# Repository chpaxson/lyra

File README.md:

# Lyra
## *6 axis robotic arm*
UC Berkeley MECENG 102B Project
Designed/built by Angel Garnica, David Gonzalez, Daniel Morales, Charles Paxson

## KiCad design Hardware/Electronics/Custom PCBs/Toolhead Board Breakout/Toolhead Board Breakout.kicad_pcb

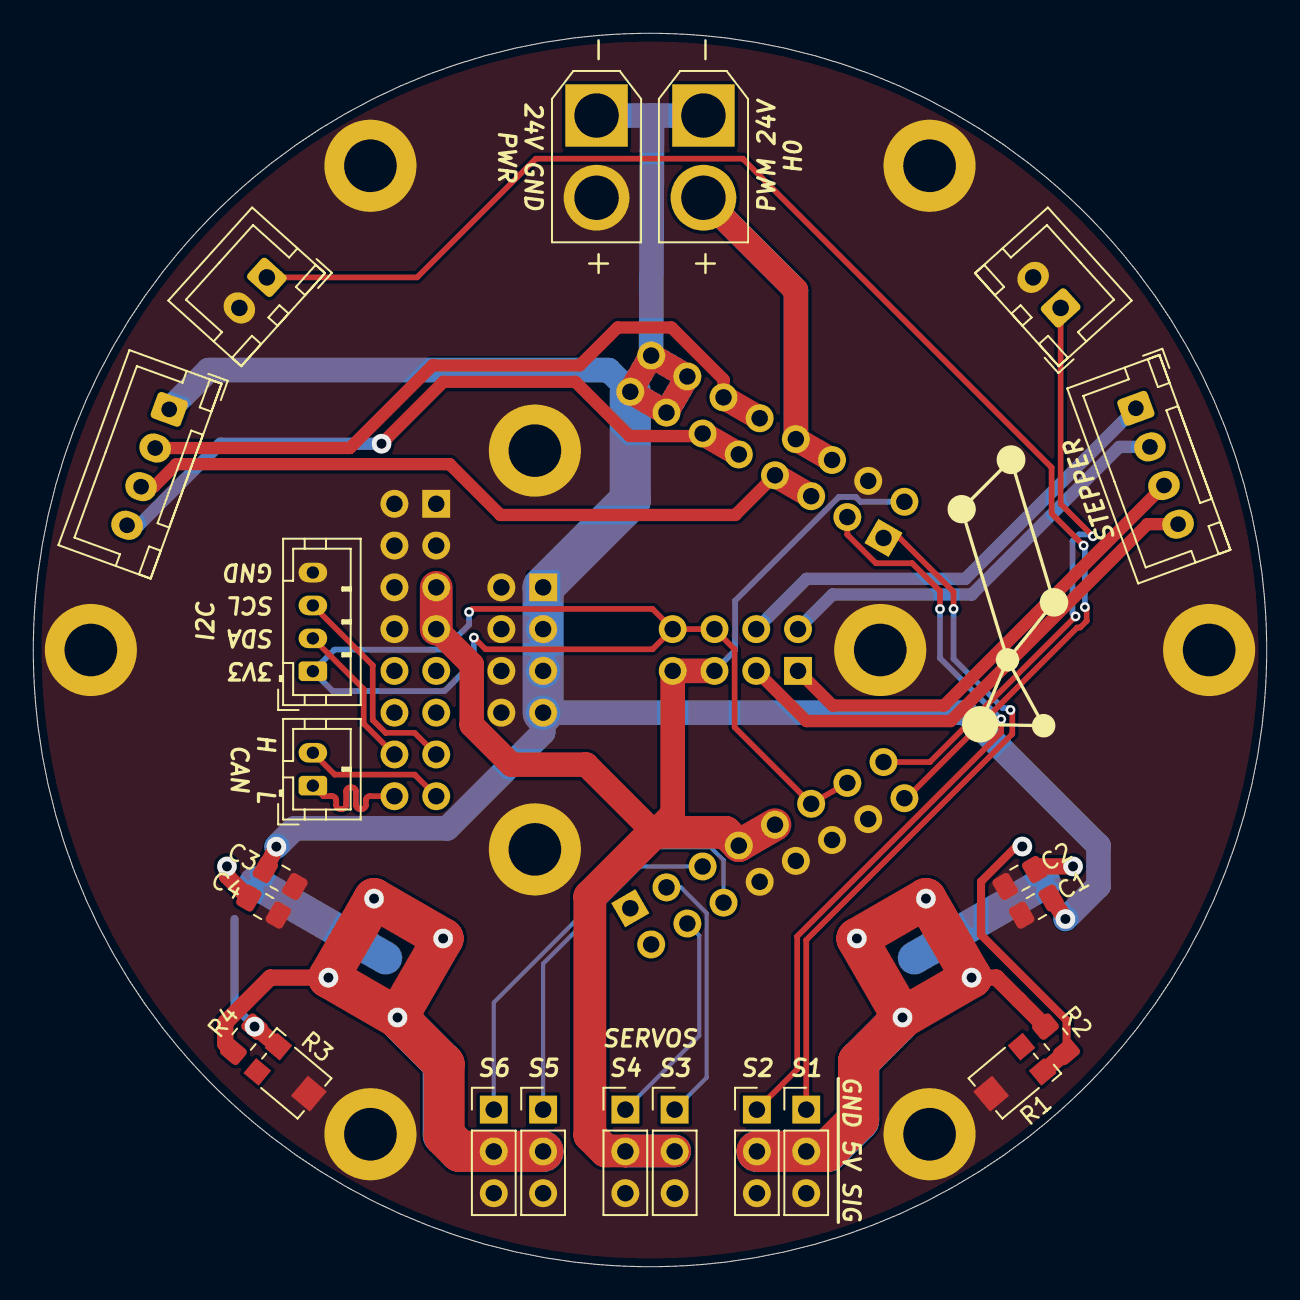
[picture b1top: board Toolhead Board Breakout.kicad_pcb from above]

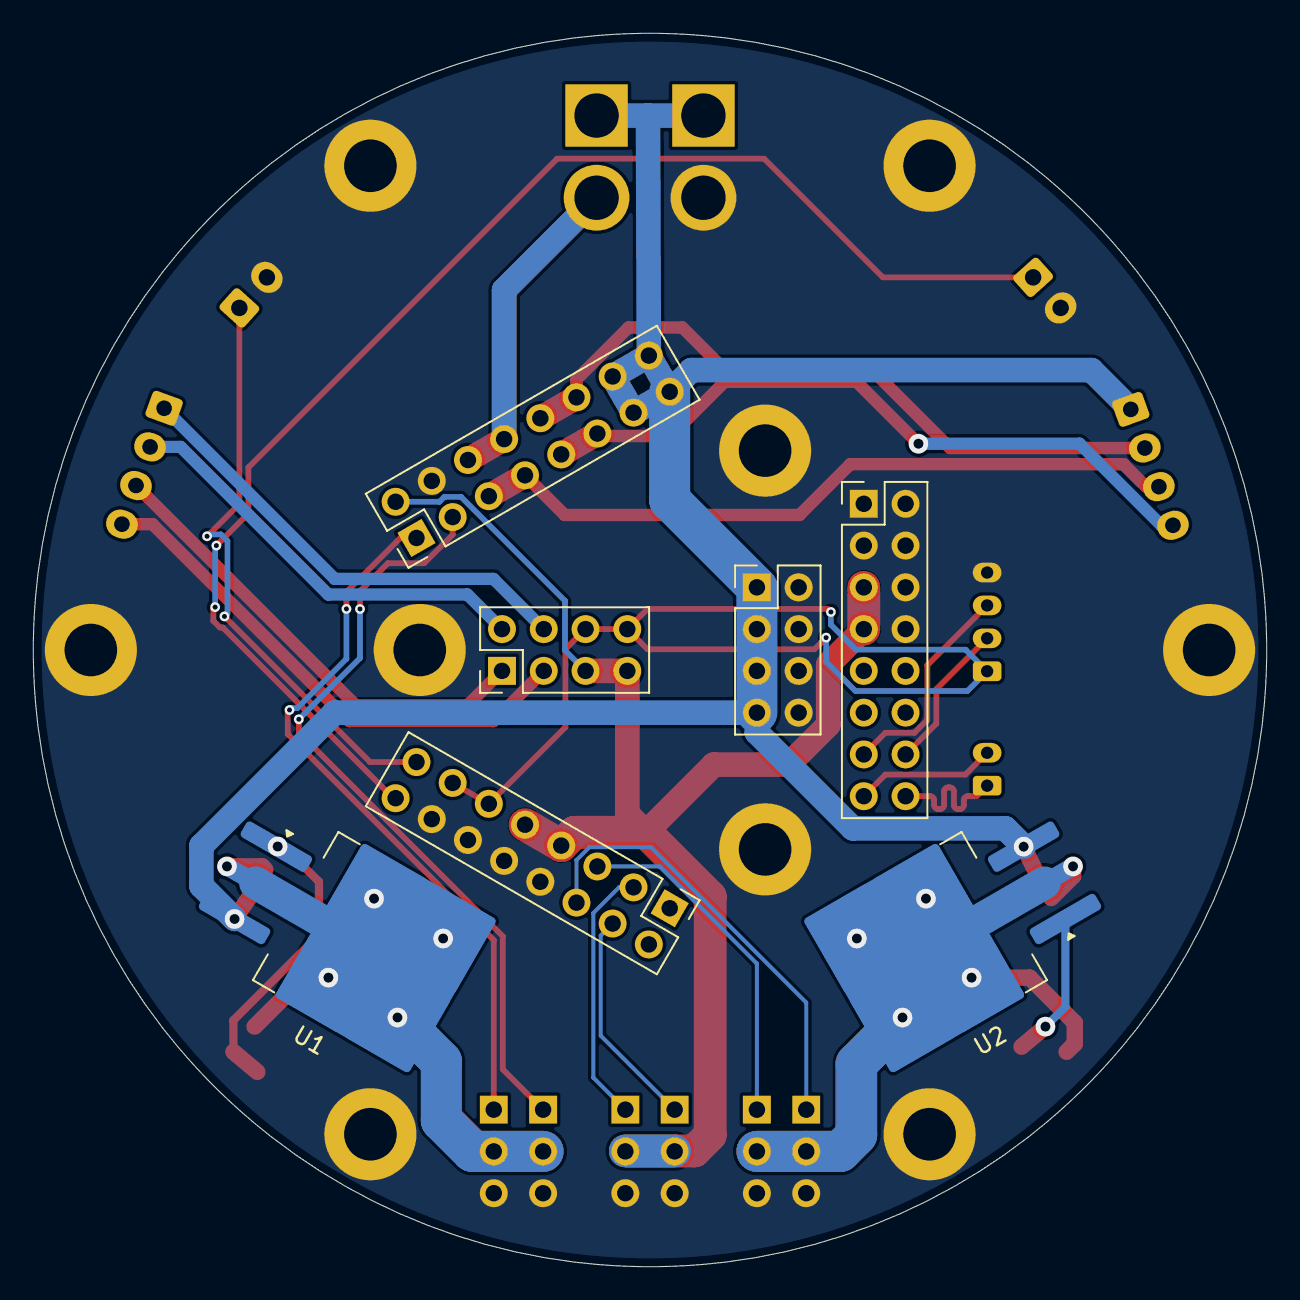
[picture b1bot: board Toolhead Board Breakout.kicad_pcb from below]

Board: 2 copper layers, 75.0 x 75.0 mm, 38 parts (7 on the bottom side), 28 nets.

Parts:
C1, C2, C3, C4: 10uF; C_0805_2012Metric_Pad1.18x1.45mm_HandSolder
H1, H1#2, H1#3, H2, H2#2, H2#3, H2#4, H2#5, H2#6: MountingHole; MountingHole_3.2mm_M3_DIN965_Pad
J1, J2, J3: Conn_02x08_Odd_Even; PinHeader_2x08_P2.54mm_Vertical
J4, J5: Conn_02x04_Odd_Even; PinHeader_2x04_P2.54mm_Vertical
J6, J22: Conn_01x04; JST_XH_B4B-XH-A_1x04_P2.50mm_Vertical
J7, J8, J9, J10, J11, J12: Conn_01x03; PinHeader_1x03_P2.54mm_Vertical
J13: Conn_01x02; JST_PH_B2B-PH-K_1x02_P2.00mm_Vertical
J14: Conn_01x04; JST_PH_B4B-PH-K_1x04_P2.00mm_Vertical
J15, J21: Conn_01x02; AMASS_XT30U-F_1x02_P5.0mm_Vertical
J17, J18: Conn_01x02; JST_XH_B2B-XH-A_1x02_P2.50mm_Vertical
R1, R3: 5k; Potentiometer_Bourns_TC33X_Vertical
R2, R4: 121; R_0805_2012Metric_Pad1.20x1.40mm_HandSolder
U1, U2: LM1084-5.0; TO-263-3_TabPin2

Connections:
5VA: C2.1, J7.2, J8.2, R2.1, U1.2 (VO)
5VB: C4.1, J11.2, J12.2, R4.1, U2.2 (VO)
24V_PWM0: J2.6, J2.8, J21.2
24V_PWM1: J2.10, J2.12, J22.2
24V_PWM2: J2.5, J2.7, J22.3
24V_PWM3: J2.9, J2.11, J22.4
+3.3V: J3.11, J3.13, J5.6, J5.8, J14.1
+5V: J1.5, J1.7, J2.2, J3.7, J3.9, J5.5, J5.7, J9.2, J10.2
+24V: C1.1, C3.1, J2.13, J2.14, J2.15, J2.16, J4.1, J4.3, J4.5, J4.7, J15.1, J21.1, J22.1, U1.3 (VI), U2.3 (VI)
CAN_H: J1.16, J13.1
CAN_L: J1.15, J13.2
GND: C1.2, C2.2, C3.2, C4.2, H1.1, H1#2.1, H1#3.1, H2.1, H2#2.1, H2#3.1, H2#4.1, H2#5.1, H2#6.1, J1.1, J1.2, J1.3, J1.4, J1.6, J1.8, J2.4, J3.8, J3.10, J3.12, J3.14, J4.2, J4.4, J4.6, J4.8, J7.3, J8.3, J9.3, J10.3, J11.3, J12.3, J14.4, J15.2, J17.2, J18.2, R1.2, R3.2
unnamed: R1.1, R2.2, U1.1 (GND)
unnamed: R3.1, R4.2, U2.1 (GND)
OA1: J5.4, J6.1
OA2: J5.2, J6.2
OB1: J5.1, J6.3
OB2: J5.3, J6.4
SCL: J1.13, J14.3
SDA: J1.14, J14.2
SERVO1: J2.1, J7.1
SERVO2: J2.3, J8.1
SERVO3: J3.3, J9.1
SERVO4: J3.4, J10.1
SERVO5: J3.5, J11.1
SERVO6: J3.6, J12.1
THERM0: J3.15, J17.1
THERM1: J3.16, J18.1

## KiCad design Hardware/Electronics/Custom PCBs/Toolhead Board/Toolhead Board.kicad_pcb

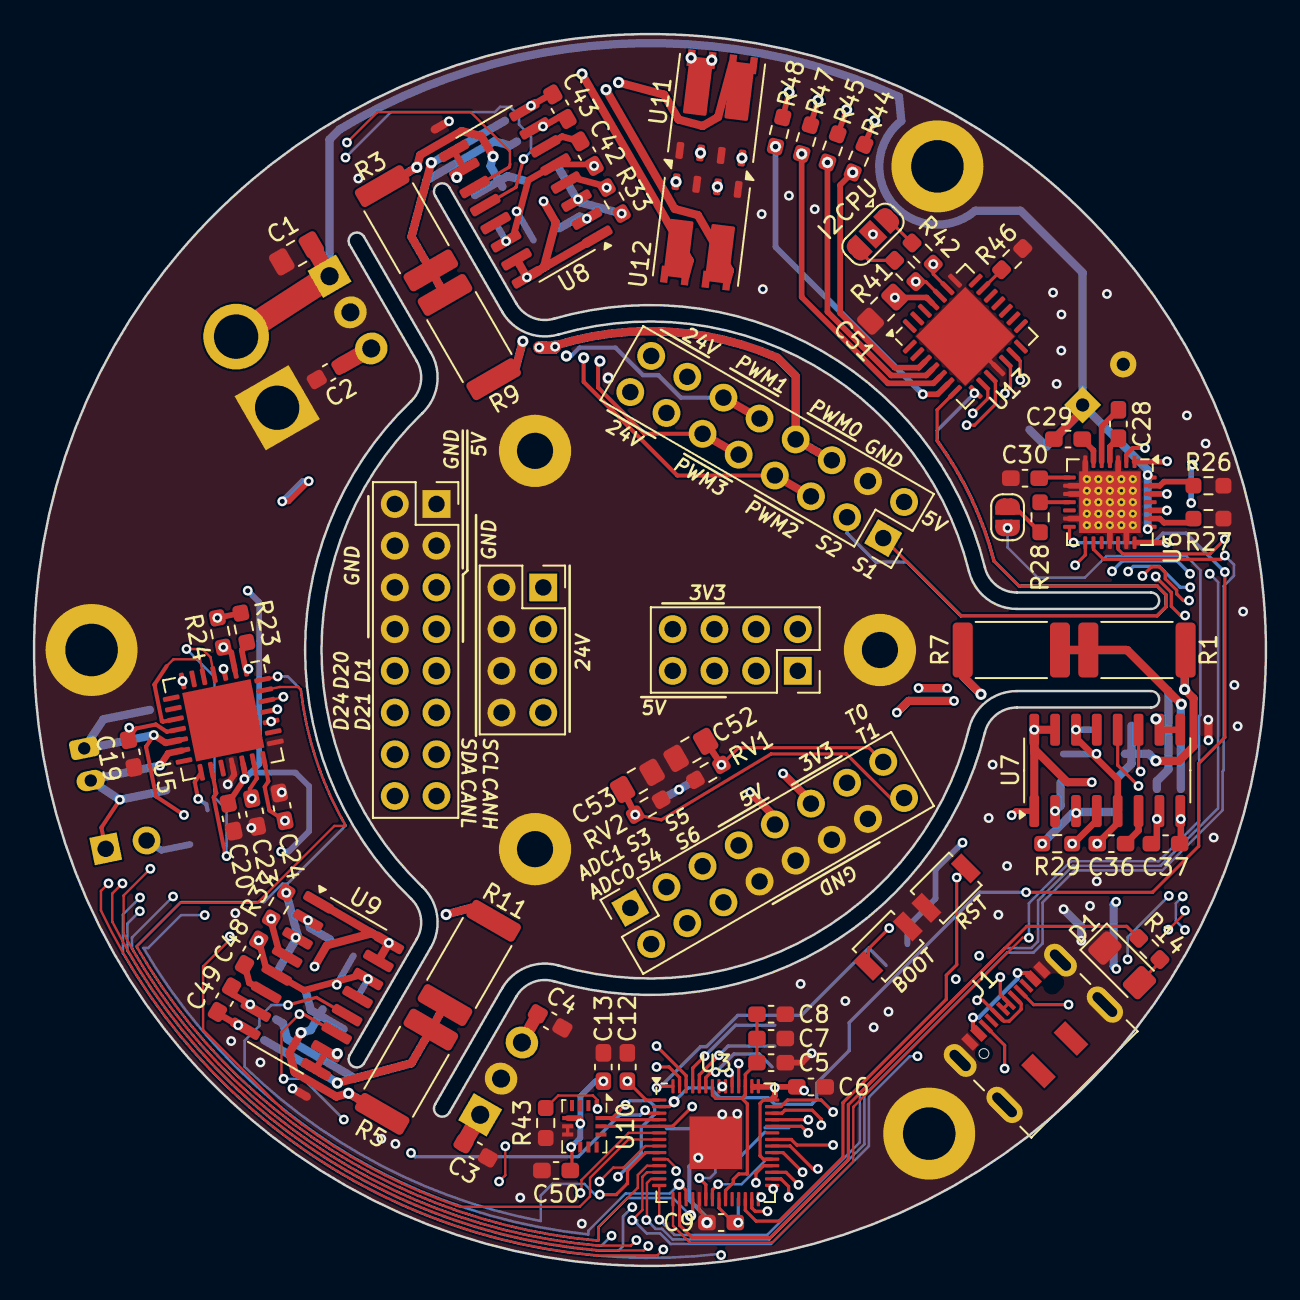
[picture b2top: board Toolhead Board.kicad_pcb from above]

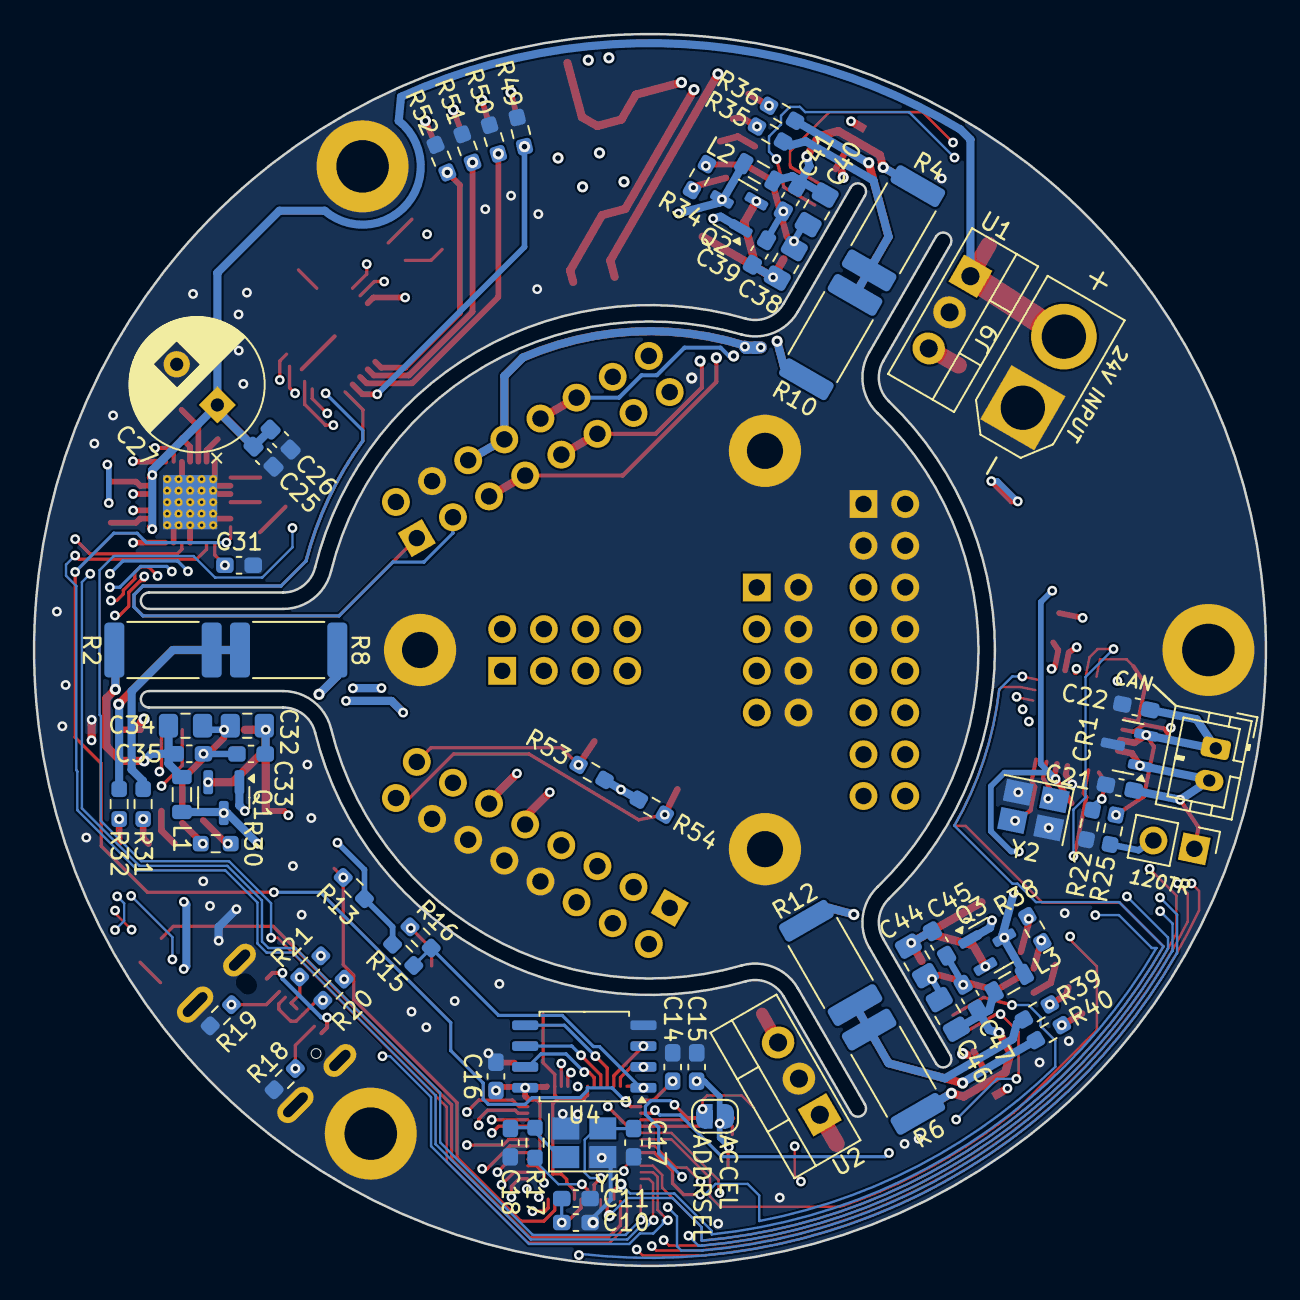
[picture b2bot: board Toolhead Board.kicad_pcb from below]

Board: 4 copper layers, 75.0 x 75.0 mm, 155 parts (72 on the bottom side), 124 nets.

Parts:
C1: 1u/100V; C_0805_2012Metric_Pad1.18x1.45mm_HandSolder
C2, C3, C4, C5, C6: 1u; C_0603_1608Metric_Pad1.08x0.95mm_HandSolder
C7, C8, C9, C10, C11, C12, C13, C14, C15, C16, C19, C20, C25, C26, C29, C31, C50: 100n; C_0603_1608Metric_Pad1.08x0.95mm_HandSolder
C17, C18, C23, C24: 22p; C_0603_1608Metric_Pad1.08x0.95mm_HandSolder
C21, C22: 47p; C_0603_1608Metric_Pad1.08x0.95mm_HandSolder
C27: 100u; CP_Radial_D8.0mm_P3.50mm
C28: 22n; C_0603_1608Metric_Pad1.08x0.95mm_HandSolder
C30: 4.7u; C_0603_1608Metric_Pad1.08x0.95mm_HandSolder
C32, C34, C38, C40, C44, C46: 10uF; C_0805_2012Metric_Pad1.18x1.45mm_HandSolder
C33, C35, C36, C37, C39, C41, C42, C43, C45, C47, C48, C49: 0.1uF; C_0603_1608Metric_Pad1.08x0.95mm_HandSolder
C51, C52, C53: 10u; C_0805_2012Metric_Pad1.18x1.45mm_HandSolder
CR1: PESD1CAN_215; SOT-23
D1: LED; LED_1206_3216Metric_Pad1.42x1.75mm_HandSolder
H1, H1#2, H1#3: MountingHole; MountingHole_3.2mm_M3_DIN965_Pad
H2, H2#2, H2#3: MountingHole; MountingHole_2.2mm_M2_Pad
J1: USB C Receptacle; USB_C_Receptacle_JAE_DX07S016JA1R1500
J2, J6: Conn_02x04_Odd_Even; PinSocket_2x04_P2.54mm_Vertical
J3, J4, J5: Conn_02x08_Odd_Even; PinSocket_2x08_P2.54mm_Vertical
J7: Conn_01x02; JST_PH_B2B-PH-K_1x02_P2.00mm_Vertical
J8: Conn_01x02; PinHeader_1x02_P2.54mm_Vertical
J9: Conn_01x02; AMASS_XT30U-F_1x02_P5.0mm_Vertical
JP1, JP3: SolderJumper_2_Open; SolderJumper-2_P1.3mm_Open_RoundedPad1.0x1.5mm
JP2: SolderJumper_3_Bridged123; SolderJumper-3_P1.3mm_Open_RoundedPad1.0x1.5mm
L1, L2, L3: 3.3uH; L_0805_2012Metric
NT1, NT2, NT3: NetTie_2; NetTie-2_SMD_Pad0.5mm
Q1, Q2, Q3: MMBT4403; SOT-23
R1, R2, R3, R4, R5, R6, R7, R8, R9, R10, R11, R12: 330; R_2512_6332Metric
R13, R14, R15, R22, R23, R24, R29, R33, R37, R43, R46, R49, R50, R51, R52: 10k; R_0603_1608Metric_Pad0.98x0.95mm_HandSolder
R16, R17: 1k; R_0603_1608Metric_Pad0.98x0.95mm_HandSolder
R18, R19: 5.1k; R_0603_1608Metric_Pad0.98x0.95mm_HandSolder
R20, R21: 27.4; R_0603_1608Metric_Pad0.98x0.95mm_HandSolder
R25: 120; R_0603_1608Metric_Pad0.98x0.95mm_HandSolder
R26, R27: 0R11; R_0603_1608Metric_Pad0.98x0.95mm_HandSolder
R28, R31, R32, R35, R36, R39, R40, R44, R45, R47, R48: 100; R_0603_1608Metric_Pad0.98x0.95mm_HandSolder
R30, R34, R38: 8.2k; R_0603_1608Metric_Pad0.98x0.95mm_HandSolder
R41, R42, R53, R54: 2.2k; R_0603_1608Metric_Pad0.98x0.95mm_HandSolder
RV1, RV2: CG0603MLC-3.3LE; R_0603_1608Metric_Pad0.98x0.95mm_HandSolder
SW1: BOOT; SW_SPST_B3U-1000P
SW2: RESET; SW_SPST_B3U-1000P
U1, U2: LF15_TO220; TO-220-3_Vertical
U3: RP2040; QFN-56-1EP_7x7mm_P0.4mm_EP3.2x3.2mm
U4: W25Q128JVS; SOIC-8_5.23x5.23mm_P1.27mm
U5: MCP25625-x-SS; QFN-28-1EP_6x6mm_P0.65mm_EP4.25x4.25mm
U6: TMC2209-LA; QFN-28-1EP_5x5mm_P0.5mm_EP3.75x3.75mm_ThermalVias
U7, U8, U9: HX711; SOIC-16_3.9x9.9mm_P1.27mm
U10: BMI270; Bosch_LGA-14_3x2.5mm_P0.5mm
U11, U12: G20N06D52; WDFN-8-1EP_6x5mm_P1.27mm_EP3.4x4mm_No_Center_Pad
U13: PCA9685BS; QFN-28-1EP_6x6mm_P0.65mm_EP4.25x4.25mm
Y1: 12MHz/12pF/50Ω/20ppm; Oscillator_SMD_SeikoEpson_SG210-4Pin_2.5x2.0mm_HandSoldering
Y2: 16MHz/12pF; Oscillator_SMD_SeikoEpson_SG210-4Pin_2.5x2.0mm_HandSoldering

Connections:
24V_PWM0: J4.6, J4.8, U11.7 (D1)
24V_PWM1: J4.10, J4.12, U11.5 (D2)
24V_PWM2: J4.5, J4.7, U12.7 (D1)
24V_PWM3: J4.9, J4.11, U12.5 (D2)
+1V1: C5.2, C7.2, C8.2, U3.23 (DVDD), U3.45 (VREG_VOUT), U3.50 (DVDD)
+3.3V: C4.1, C6.1, C9.2, C10.2, C11.2, C12.2, C13.2, C14.2, C15.2, C16.1, C19.2, C31.1, C32.1, C33.1, C38.1, C39.1, C44.1, C45.1, C50.1, J5.11, J5.13, J6.6, J6.8, JP2.2 (C), JP3.1 (A), Q1.2 (E), Q2.2 (E), Q3.2 (E), R13.1, R15.2, R23.1, R24.2, R53.1, R54.1, U2.3 (VO), U3.1 (IOVDD), U3.10 (IOVDD), U3.22 (IOVDD), U3.33 (IOVDD), U3.42 (IOVDD), U3.43 (ADC_AVDD), U3.44 (VREG_IN), U3.48 (USB_VDD), U3.49 (IOVDD), U4.8 (VCC), U5.3 (VDD), U5.11 (VIO), U6.15 (VCC_IO), U7.1 (VSUP), U7.15 (RATE), U7.16 (DVDD), U8.1 (VSUP), U8.15 (RATE), U8.16 (DVDD), U9.1 (VSUP), U9.15 (RATE), U9.16 (DVDD), U10.5 (VDDIO), U10.8 (VDD)
+5V: C2.1, C3.1, C20.1, C51.2, J3.5, J3.7, J4.2, J5.7, J5.9, J6.5, J6.7, U1.3 (VO), U2.1 (VI), U5.19 (VDDA), U13.25 (VDD)
/Accelerometer/Address Selection: JP3.2 (B), R43.1, U10.1 (SDO)
/Microcontroller/LED: R14.2, U3.16 (GPIO13)
/Microcontroller/QSPI_SCK: U3.52 (QSPI_SCLK), U4.6 (CLK)
/Microcontroller/QSPI_SD0: U3.53 (QSPI_SD0), U4.5 (DI(IO0))
/Microcontroller/QSPI_SD1: U3.55 (QSPI_SD1), U4.2 (DO(IO1))
/Microcontroller/QSPI_SD2: U3.54 (QSPI_SD2), U4.3 (IO2)
/Microcontroller/QSPI_SD3: U3.51 (QSPI_SD3), U4.7 (IO3)
/Microcontroller/QSPI_SS: R15.1, R16.2, U3.56 (QSPI_SS), U4.1 (~CS)
/Microcontroller/RUN: R13.2, SW2.2, U3.26 (RUN)
/Microcontroller/USB+: R20.2, U3.47 (USB_DP)
/Microcontroller/USB-: R21.1, U3.46 (USB_DM)
/Microcontroller/~USB_BOOT: R16.1, SW1.2
ADC0: J5.2, U3.38 (GPIO26_ADC0)
ADC1: J5.1, U3.39 (GPIO27_ADC1)
CAN_CS: R23.2, U3.30 (GPIO19), U5.1 (~CS)
CAN_H: C21.1, CR1.1, J3.16, J7.2, J8.1, U5.13 (CANH)
CAN_INT: U3.34 (GPIO22), U5.25 (~INT)
CAN_L: C22.1, CR1.2, J3.15, J7.1, R25.2, U5.12 (CANL)
CAN_RST: R24.1, U3.29 (GPIO18), U5.2 (~RESET)
CAN_STBY: R22.2, U3.27 (GPIO16), U5.15 (STBY)
D1: J3.9, U3.3 (GPIO1)
D20: J3.10, U3.31 (GPIO20)
D21: J3.11, U3.32 (GPIO21)
D24: J3.12, U3.36 (GPIO24)
GND: C1.1, C2.2, C3.2, C4.2, C5.1, C6.2, C7.1, C8.1, C9.1, C10.1, C11.1, C12.1, C13.1, C14.1, C15.1, C16.2, C17.1, C18.1, C19.1, C20.2, C21.2, C22.2, C23.1, C24.2, C25.2, C26.2, C27.2, C30.1, C31.2, C50.2, C51.1, C52.2, C53.2, CR1.3, D1.1 (K), H1.1, H1#2.1, H1#3.1, H2.1, H2#2.1, H2#3.1, J1.A1 (GND), J1.A12 (GND), J1.B1 (GND), J1.B12 (GND), J1.S1 (SHIELD), J2.2, J2.4, J2.6, J2.8, J3.1, J3.2, J3.3, J3.4, J3.6, J3.8, J4.4, J5.8, J5.10, J5.12, J5.14, J9.1, NT1.2, NT2.2, NT3.2, R18.2, R19.2, R22.1, R26.2, R27.1, R43.2, R46.1, R49.1, R50.1, R51.1, R52.1, RV1.2, RV2.2, SW1.1, SW2.1, U1.2 (GND), U2.2 (GND), U3.19 (TESTEN), U3.57 (GND), U4.4 (GND), U5.18 (VSS), U5.22 (GND), U6.3 (GND), U6.7 (SPREAD), U6.9 (MS1_AD0), U6.10 (MS2_AD1), U6.13 (CLK), U6.18 (GND), U6.20 (STDBY), U6.29 (GND), U10.6 (GNDIO), U10.7 (GND), U11.1 (S1), U11.3 (S2), U12.1 (S1), U12.3 (S2), U13.11 (VSS), U13.22 (EXTCLK), U13.29 (VSS), Y1.2, Y1.4, Y2.2, Y2.4
MISO: U3.11 (GPIO8), U5.27 (SI)
MOSI: U3.18 (GPIO15), U5.28 (SO)
MOT_DIAG: JP1.1 (A), U3.15 (GPIO12)
MOT_DIR: U3.14 (GPIO11), U6.19 (DIR)
MOT_EN: U3.12 (GPIO9), U6.2 (ENN)
MOT_STP: U3.13 (GPIO10), U6.16 (STEP)
MOT_UART: U3.2 (GPIO0), U6.14 (PDN_UART)
unnamed: C18.2, R17.1, Y1.1
unnamed: D1.2 (A), R14.1
unnamed: J1.A5 (CC1), R18.1
unnamed: J1.B5 (CC2), R19.1
unnamed: J1.A6 (D+), J1.B6 (D+), R21.2
unnamed: J1.A7 (D-), J1.B7 (D-), R20.1
unnamed: J8.2, R25.1
unnamed: JP1.2 (B), R28.1
unnamed: JP2.1 (A), R42.1
unnamed: JP2.3 (B), R41.1
unnamed: Q1.1 (B), U7.2 (BASE)
unnamed: L1.1, Q1.3 (C), R29.1, U7.3 (AVDD)
unnamed: Q2.1 (B), U8.2 (BASE)
unnamed: L2.1, Q2.3 (C), R33.1, U8.3 (AVDD)
unnamed: Q3.1 (B), U9.2 (BASE)
unnamed: L3.1, Q3.3 (C), R37.1, U9.3 (AVDD)
unnamed: C17.2, U3.20 (XIN), Y1.3
unnamed: R17.2, U3.21 (XOUT)
unnamed: C24.1, U5.21 (OSC1), Y2.3
unnamed: C23.2, U5.20 (OSC2), Y2.1
unnamed: U5.5 (RxCAN), U5.10 (RXD)
unnamed: U5.4 (TxCAN), U5.16 (TXD)
unnamed: C30.2, U6.8 (5VOUT)
unnamed: R27.2, U6.23 (BRA)
unnamed: R26.1, U6.27 (BRB)
unnamed: C28.1, U6.5 (CPI)
unnamed: C28.2, U6.4 (CPO)
unnamed: R28.2, U6.11 (DIAG)
unnamed: C29.2, U6.6 (VCP)
unnamed: C37.1, R32.2, U7.8 (INA+)
unnamed: C37.2, R31.1, U7.7 (INA-)
unnamed: C36.2, U7.6 (VBG)
unnamed: R29.2, R30.1, U7.4 (VFB)
unnamed: C43.1, R36.2, U8.8 (INA+)
unnamed: C43.2, R35.1, U8.7 (INA-)
unnamed: C42.2, U8.6 (VBG)
unnamed: R33.2, R34.1, U8.4 (VFB)
unnamed: C49.1, R40.2, U9.8 (INA+)
unnamed: C49.2, R39.1, U9.7 (INA-)
unnamed: C48.2, U9.6 (VBG)
unnamed: R37.2, R38.1, U9.4 (VFB)
unnamed: R44.2, U11.2 (G1)
unnamed: R45.2, U11.4 (G2)
unnamed: R47.2, U12.2 (G1)
unnamed: R48.2, U12.4 (G2)
unnamed: R44.1, R52.2, U13.3 (LED0)
unnamed: R45.1, R51.2, U13.4 (LED1)
unnamed: R47.1, R50.2, U13.5 (LED2)
unnamed: R48.1, R49.2, U13.6 (LED3)
unnamed: R46.2, U13.20 (~OE)
OA1: J6.4, U6.24 (OA1)
OA2: J6.2, U6.21 (OA2)
OB1: J6.1, U6.26 (OB1)
OB2: J6.3, U6.1 (OB2)
RX0BF: U3.35 (GPIO23), U5.24 (~Rx0BF)
SCK: U3.17 (GPIO14), U5.26 (SCK)
SCL: J3.13, R42.2, U3.5 (GPIO3), U10.13 (SCX), U13.23 (SCL)
SDA: J3.14, R41.2, U3.4 (GPIO2), U10.14 (SDX), U13.24 (SDA)
SERVO1: J4.1, U13.7 (LED4)
SERVO2: J4.3, U13.8 (LED5)
SERVO3: J5.3, U13.9 (LED6)
SERVO4: J5.4, U13.10 (LED7)
SERVO5: J5.5, U13.12 (LED8)
SERVO6: J5.6, U13.13 (LED9)
STRAIN1_DO: U3.6 (GPIO4), U7.12 (DOUT)
STRAIN1_E+: C34.1, C35.1, L1.2, R1.1, R2.2
STRAIN1_E-: C32.2, C33.2, C34.2, C35.2, C36.1, NT1.1, R7.2, R8.1, R30.2, U7.5 (AGND), U7.9 (INB-), U7.10 (INB+), U7.14 (XI)
STRAIN1_S+: R1.2, R7.1, R32.1
STRAIN1_S-: R2.1, R8.2, R31.2
STRAIN2_DO: U3.7 (GPIO5), U8.12 (DOUT)
STRAIN2_E+: C40.1, C41.1, L2.2, R3.1, R4.2
STRAIN2_E-: C38.2, C39.2, C40.2, C41.2, C42.1, NT2.1, R9.2, R10.1, R34.2, U8.5 (AGND), U8.9 (INB-), U8.10 (INB+), U8.14 (XI)
STRAIN2_S+: R3.2, R9.1, R36.1
STRAIN2_S-: R4.1, R10.2, R35.2
STRAIN3_DO: U3.9 (GPIO7), U9.12 (DOUT)
STRAIN3_E+: C46.1, C47.1, L3.2, R5.1, R6.2
STRAIN3_E-: C44.2, C45.2, C46.2, C47.2, C48.1, NT3.1, R11.2, R12.1, R38.2, U9.5 (AGND), U9.9 (INB-), U9.10 (INB+), U9.14 (XI)
STRAIN3_S+: R5.2, R11.1, R40.1
STRAIN3_S-: R6.1, R12.2, R39.2
STRAIN_SCK: U3.8 (GPIO6), U7.11 (PD_SCK), U8.11 (PD_SCK), U9.11 (PD_SCK)
THERM0: C52.1, J5.15, R53.2, RV1.1, U3.40 (GPIO28_ADC2)
THERM1: C53.1, J5.16, R54.2, RV2.1, U3.41 (GPIO29_ADC3)
TX0RTS: U3.28 (GPIO17), U5.7 (~Tx0RTS)
VBUS: J1.A4 (VBUS), J1.A9 (VBUS), J1.B4 (VBUS), J1.B9 (VBUS)
V_MOT: C1.2, C25.1, C26.1, C27.1, C29.1, J2.1, J2.3, J2.5, J2.7, J4.13, J4.14, J4.15, J4.16, J9.2, U1.1 (VI), U6.22 (VS), U6.28 (VS)

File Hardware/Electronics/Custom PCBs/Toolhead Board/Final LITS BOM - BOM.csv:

Partner 1 Name: Charles Paxson,Partner 1 Email: chpaxson@berkeley.edu,Partner 2 Name: David Gonzalez,Partner 2 Email: davgon612@berkeley.edu,,,,,,,,
,,,,,,,,,,,
"We filled out the ""Multiple"" column for a few components that we already have some of.",,,,,,,,,,,Total Price for Project
,,,,,,,,,,,$136.75
"Qty
(for 1 board)",Manufacturer Part #,Digi-key Part#/SKU,Mouser Part#/SKU,Price/unit ($),Purchase URL,"Reference
Designator","Description
(include component value if applicable)",Datasheet Link,Multiple,Total Qty,Total Price/part ($)
1,GMC21X7R105K50NT,4713-GMC21X7R105K50NTCT-ND,,$0.16,https://www.digikey.com/en/products/detail/cal-chip-electron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,C1,1 uF (50V) 0805 Capacitor,,3,3,$0.48
5,CL10A105KA8NNNC,1276-1102-1-ND,,$0.03,https://www.digikey.com/en/products/detail/samsung-electro-m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,C2-C6,1 uF (25V) 0603 Capacitor,,3,15,$0.45
29,CL10B104KB8NNWC,1276-1935-1-ND,,$0.01,https://www.digikey.com/en/products/detail/samsung-electro-m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,"C7-C16, C19, C20, C25, C26, C29, C31, C33, C35-C37, C39, C41-C43, C45, C47-C50",100 nF (50V) 0603 Capacitor,,3,87,$0.89
5,KGM15ACG1C220KT,478-KGM15ACG1C220KTCT-ND,,$0.03,https://www.digikey.com/en/products/detail/kyocera-avx/KGM15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,"C17, C18, C23, C24",22 pF (16V) 0603 Capacitor,,3,15,$0.42
5,CC0603KRNPO9BN470,311-4037-1-ND,,$0.05,https://www.digikey.com/en/products/detail/yageo/CC0603KRNPO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,"C21, C22",47 pF (50V) 0603 Capacitor,,3,15,$0.74
1,ECA-1HM101,P5182-ND,,$0.39,https://www.digikey.com/en/products/detail/panasonic-electro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,C27,100 uF (50V) Radial Capacitor,,3,3,$1.17
1,0603B223K500CT,1292-1417-1-ND,,$0.10,https://www.digikey.com/en/products/detail/walsin-technology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,C28,22 pF (50V) 0603 Capacitor,,3,3,$0.30
1,CL10A475KP8NNNC,1276-1044-1-ND,,$0.10,https://www.digikey.com/en/products/detail/samsung-electro-m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,C30,4.7 uF (10V) 0603 Capacitor,,3,3,$0.30
9,CL21A106KAYNNNE,1276-2891-1-ND,,$0.12,https://www.digikey.com/en/products/detail/samsung-electro-m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,"C32, C34, C38, C40, C44, C46, C51-C53",10 uF (25V) 0805 Capacitor,,3,27,$3.29
1,PESD1CAN,5272-PESD1CANCT-ND,,$0.36,https://www.digikey.com/en/products/detail/evvo/PESD1CAN/224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,CR1,CAN ESD Protection Diode,,3,3,$1.08
1,QTLP650D4TR,1080-1419-1-ND,,$0.41,https://www.digikey.com/en/products/detail/everlight-electro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,D1,Indicator LED,,5,5,$2.05
1,DX07S016JA1R1500,670-DX07S016JA1R1500TR-ND,,$1.80,https://www.digikey.com/en/products/detail/jae-electronics/d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,J1,USB Port,,3,3,$5.40
2,PPTC042LFBN-RC,S7072-ND,,$0.68,https://www.digikey.com/en/products/detail/sullins-connector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,"J2, J6","2x4 0.1"" Female Pin Header",,3,6,$4.08
3,PPTC082LFBN-RC,S7076-ND,,$1.00,https://www.digikey.com/en/products/detail/sullins-connector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,J3-J5,"2x8 0.1"" Female Pin Header",,3,9,$9.00
1,B2B-PH-K-S,455-1704-ND,,$0.19,https://www.digikey.com/en/products/detail/jst-sales-america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,J7,JST-PH 1x2 - CAN Input,,3,3,$0.57
1,61300211121,732-5315-ND,,$0.13,https://www.digikey.com/en/products/detail/w%C3%BCrth-elektr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,J8,"1x2 0.1"" Male Pin Header",,3,3,$0.39
1,FIT0586,1738-1436-ND,,$1.90,https://www.digikey.com/en/products/detail/dfrobot/FIT0586/9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,J9,XT30 - 24V Input,,3,3,$5.70
3,MLZ2012A3R3WTD25,445-16375-1-ND,,$0.15,https://www.digikey.com/en/products/detail/tdk-corporation/M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,L1-L3,3.3 uH (450mA) 0805 Inductor,,3,9,$1.35
3,MMBT4403LT1G,MMBT4403LT1GOSCT-ND,,$0.09,https://www.digikey.com/en/products/detail/onsemi/MMBT4403LT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,Q1-Q3,PNP transistor (40V),,3,9,$0.83
12,RMCF2512JT330R,RMCF2512JT330RCT-ND,,$0.12,https://www.digikey.com/en/products/detail/stackpole-electro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,R1-R12,330Ω (1W) resistor,,3,36,$4.25
15,WR06X103 JTL,1292-WR06X103JTLCT-ND,,$0.01,https://www.digikey.com/en/products/detail/walsin-technology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,"R13-R15, R22-R24, R29, R33, R37, R43, R46, R49-R52",10kΩ (0.1W) resistor,,3,45,$0.54
2,RC0603FR-071KL,311-1.00KHRCT-ND,,$0.10,https://www.digikey.com/en/products/detail/yageo/RC0603FR-07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,"R16, R17",1kΩ (0.1W) resistor,,3,6,$0.60
2,RC0603FR-075K1L,311-5.10KHRCT-ND,,$0.10,https://www.digikey.com/en/products/detail/yageo/RC0603FR-07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,"R18, R19",5.1kΩ (0.1W) resistor,,3,6,$0.60
2,RMCF0603FT27R4,RMCF0603FT27R4CT-ND,,$0.10,https://www.digikey.com/en/products/detail/stackpole-electro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,"R20, R21",27.4Ω (0.1W) resistor,,3,6,$0.60
1,RMCF0603FT120R,RMCF0603FT120RCT-ND,,$0.10,https://www.digikey.com/en/products/detail/stackpole-electro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,R25,120Ω (0.1W) resistor,,3,3,$0.30
11,RC0603FR-07100RL,311-100HRCT-ND,,$0.02,https://www.digikey.com/en/products/detail/yageo/RC0603FR-07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,"R28, R31, R32, R35, R36, R39, R40, R44, R45, R47, R48",100Ω (0.1W) resistor,,3,33,$0.63
3,RC0603JR-078K2L,311-8.2KGRCT-ND,,$0.02,https://www.digikey.com/en/products/detail/yageo/RC0603JR-07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,"R30, R34, R38",8.2kΩ (0.1W) resistor,,3,9,$0.14
4,RMCF0603FT2K20,RMCF0603FT2K20CT-ND,,$0.02,https://www.digikey.com/en/products/detail/stackpole-electro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,"R41, R42, R53, R54",2.2kΩ (0.1W) resistor,,3,12,$0.18
2,CG0603MLC-3.3LE,CG0603MLC-3.3LECT-ND,,$0.37,https://www.digikey.com/en/products/detail/bourns-inc/CG0603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,"RV1, RV2",Thermistor ESD Protection 0603 Varistor,,3,6,$2.22
2,B3U-1000P,SW1020CT-ND,,$1.02,https://www.digikey.com/en/products/detail/omron-electronics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,SW1-2,RESET and BOOTSEL buttons,,3,6,$6.12
1,LD1085V50,497-3436-5-ND,,$1.77,https://www.digikey.com/en/products/detail/stmicroelectronic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,U1,24V -> 5V (3A) LDO,,2,2,$3.54
1,LD1117AV33,497-1485-5-ND,,$0.79,https://www.digikey.com/en/products/detail/stmicroelectronic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,U2,5V -> 3.3V (1A) LDO,,2,2,$1.58
1,SC0914(13),2648-SC0914(13)CT-ND,,$0.70,https://www.digikey.com/en/products/detail/raspberry-pi/SC09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,U3,RP2040 MCU,,2,2,$1.40
1,W25Q128JVSIQ,W25Q128JVSIQ-ND,,$1.73,https://www.digikey.com/en/products/detail/winbond-electroni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,U4,128MB Flash Module,,2,2,$3.46
1,MCP25625T-E/ML,MCP25625T-E/MLCT-ND,,$3.38,https://www.digikey.com/en/products/detail/microchip-technol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,U5,CAN Controller+Transceiver,,2,2,$6.76
1,TMC2209-LA,505-TMC2209-LA-ND,,$2.47,https://www.digikey.com/en/products/detail/analog-devices-in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,U6,Stepper Driver,,3,3,$7.41
1,B07SGPX7ZH,,,$8.29,https://www.amazon.com/dp/B07SGPX7ZH,U7-U9,Load Cell Amplifiers,,2,2,$16.58
1,BMI270,828-1091-1-ND,,$5.88,https://www.digikey.com/en/products/detail/bosch-sensortec/B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,U10,Accelerometer,,3,3,$17.64
2,3141-G20N06D52CT-ND,3141-G20N06D52CT-ND,,$0.68,https://www.digikey.com/en/products/detail/goford-semiconduc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,U11-12,MOSFET,,3,6,$4.08
1,"PCA9685BS,118",568-5305-1-ND,,$2.97,https://www.digikey.com/en/products/detail/nxp-usa-inc/PCA96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,U13,PWM Controller,,3,3,$8.91
1,ECS-2033-120-BN,XC1426CT-ND,,$0.76,https://www.digikey.com/en/products/detail/ecs-inc/ECS-2033-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,Y1,MCU Oscillator (12MHz),,3,3,$2.28
1,ECS-2033-160-BN,XC1430CT-ND,,$2.82,https://www.digikey.com/en/products/detail/ecs-inc/ECS-2033-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,Y2,CAN Controller Oscillator (16MHz),,3,3,$8.46

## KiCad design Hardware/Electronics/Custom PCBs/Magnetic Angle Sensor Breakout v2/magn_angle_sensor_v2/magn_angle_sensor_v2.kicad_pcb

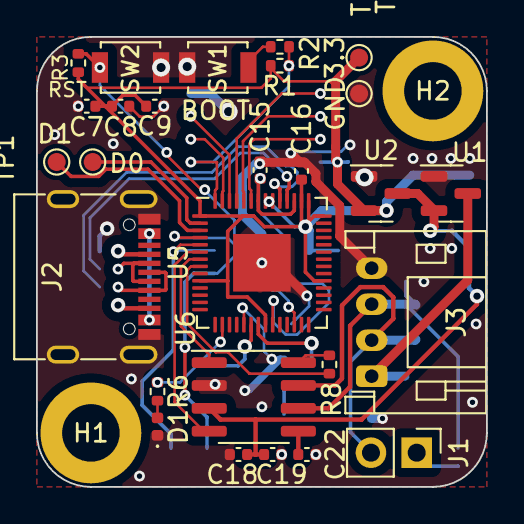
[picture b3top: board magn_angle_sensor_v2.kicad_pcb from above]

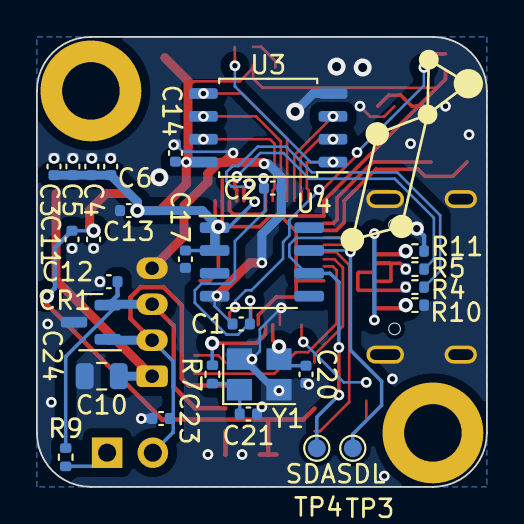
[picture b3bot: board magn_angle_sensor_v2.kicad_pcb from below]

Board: 2 copper layers, 25.0 x 25.0 mm, 57 parts (28 on the bottom side), 37 nets.

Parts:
C1, C2, C3, C4, C5, C6, C7, C8, C9, C14, C17, C19, C22: 100n; C_0402_1005Metric
C10: 1u/100V; C_0805_2012Metric
C11, C12, C13, C15, C16, C18: 1u; C_0402_1005Metric
C20, C21: 22p; C_0402_1005Metric
C23, C24: 47p; C_0402_1005Metric
CR1: PESD1CAN_215; SOT-23
D1: LED; LED_0402_1005Metric
H1, H2: MountingHole; MountingHole_3.2mm_M3_DIN965_Pad
J1: 120TR; PinHeader_1x02_P2.54mm_Vertical
J2: USB C Receptacle; USB_C_Receptacle_G-Switch_GT-USB-7010ASV
J3: JST PH 01x04; JST_PH_S4B-PH-K_1x04_P2.00mm_Horizontal
R1: 10K; R_0402_1005Metric
R2: 1K; R_0402_1005Metric
R3, R6: 10k; R_0402_1005Metric
R4, R5: 27.4; R_0402_1005Metric
R7: 1k; R_0402_1005Metric
R8: NC; R_0402_1005Metric
R9: 120; R_0402_1005Metric
R10, R11: 5.1k; R_0402_1005Metric
SW1: BOOT; SW_SPST_B3U-1000P
SW2: RESET; SW_SPST_B3U-1000P
TP1: D0; TestPoint_Pad_D1.0mm
TP2: D1; TestPoint_Pad_D1.0mm
TP3: SCL; TestPoint_Pad_D1.0mm
TP4: SDA; TestPoint_Pad_D1.0mm
TP5: 3.3V; TestPoint_Pad_D1.0mm
TP6: GND; TestPoint_Pad_D1.0mm
U1: SE8650X2-HF; SOT-23
U2: XC6206P332MR; SOT-23
U3: W25Q128JVS; SOIC-8_5.23x5.23mm_P1.27mm
U4: MT6701-CT; SOP-8_3.9x4.9mm_P1.27mm
U5: RP2040; QFN-56-1EP_7x7mm_P0.4mm_EP3.2x3.2mm
U6: SN65HVD1050D; SOIC-8_3.9x4.9mm_P1.27mm
Y1: 12MHz/12pF/50Ω/20ppm; Crystal_SMD_3225-4Pin_3.2x2.5mm

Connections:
+1V1: C1.2, C2.2, C15.2, U5.23 (DVDD), U5.45 (VREG_VOUT), U5.50 (DVDD)
+3.3V: C3.2, C4.2, C5.2, C6.2, C7.2, C8.2, C9.2, C13.1, C14.1, C16.1, C17.1, R1.2, R3.1, TP5.1, U2.2 (VO), U3.8 (VCC), U4.1 (VDD), U4.2 (MODE), U5.1 (IOVDD), U5.10 (IOVDD), U5.22 (IOVDD), U5.33 (IOVDD), U5.42 (IOVDD), U5.43 (ADC_AVDD), U5.44 (VREG_IN), U5.48 (USB_VDD), U5.49 (IOVDD)
+5V: C11.1, C12.1, C18.2, C19.2, U1.2 (VO), U2.3 (VI), U6.3 (VCC)
+24V: C10.2, J3.1, U1.3 (VI)
/CAN_H: C23.1, CR1.1, J1.2, J3.2, U6.7 (CANH)
/CAN_L: C24.1, CR1.2, J3.3, R9.2, U6.6 (CANL)
/CAN_RX: U5.6 (GPIO4), U6.4 (RXD)
/CAN_S: R8.2, U5.8 (GPIO6)
/CAN_TX: U5.7 (GPIO5), U6.1 (TXD)
/LED: R6.2, U5.16 (GPIO13)
/QSPI_SCK: U3.6 (CLK), U5.52 (QSPI_SCLK)
/QSPI_SD0: U3.5 (DI(IO0)), U5.53 (QSPI_SD0)
/QSPI_SD1: U3.2 (DO(IO1)), U5.55 (QSPI_SD1)
/QSPI_SD2: U3.3 (IO2), U5.54 (QSPI_SD2)
/QSPI_SD3: U3.7 (IO3), U5.51 (QSPI_SD3)
/QSPI_SS: R1.1, R2.2, U3.1 (~CS), U5.56 (QSPI_SS)
/RUN: R3.2, SW2.2, U5.26 (RUN)
/SCL: TP3.1, U4.7 (B/V/SCL/CLK), U5.5 (GPIO3)
/SDA: TP4.1, U4.6 (A/U/SDA/DO), U5.4 (GPIO2)
/USB_D+: J2.A6 (D+), J2.B6 (D+), R4.1
/USB_D-: J2.A7 (D-), J2.B7 (D-), R5.2
/~USB_BOOT: R2.1, SW1.2
GND: C1.1, C2.1, C3.1, C4.1, C5.1, C6.1, C7.1, C8.1, C9.1, C10.1, C11.2, C12.2, C13.2, C14.2, C15.1, C16.2, C17.2, C18.1, C19.1, C20.1, C21.1, C22.2, C23.2, C24.2, CR1.3, D1.1 (K), J2.A1 (GND), J2.A12 (GND), J2.B1 (GND), J2.B12 (GND), J2.S1 (SHIELD), J3.4, R10.2, R11.2, SW1.1, SW2.1, TP6.1, U1.1 (GND), U2.1 (GND), U3.4 (GND), U4.4 (GND), U5.19 (TESTEN), U5.57 (GND), U6.2 (GND), Y1.2, Y1.4
unnamed: C21.2, R7.1, Y1.1
unnamed: D1.2 (A), R6.1
unnamed: J1.1, R9.1
unnamed: J2.A5 (CC1), R11.1
unnamed: J2.B5 (CC2), R10.1
unnamed: TP1.1, U5.2 (GPIO0)
unnamed: TP2.1, U5.3 (GPIO1)
unnamed: R5.1, U5.46 (USB_DM)
unnamed: R4.2, U5.47 (USB_DP)
unnamed: C20.2, U5.20 (XIN), Y1.3
unnamed: R7.2, U5.21 (XOUT)
unnamed: R8.1, U6.8 (S)
unnamed: C22.1, U6.5 (VREF)
VBUS: J2.A4 (VBUS), J2.A9 (VBUS), J2.B4 (VBUS), J2.B9 (VBUS)
